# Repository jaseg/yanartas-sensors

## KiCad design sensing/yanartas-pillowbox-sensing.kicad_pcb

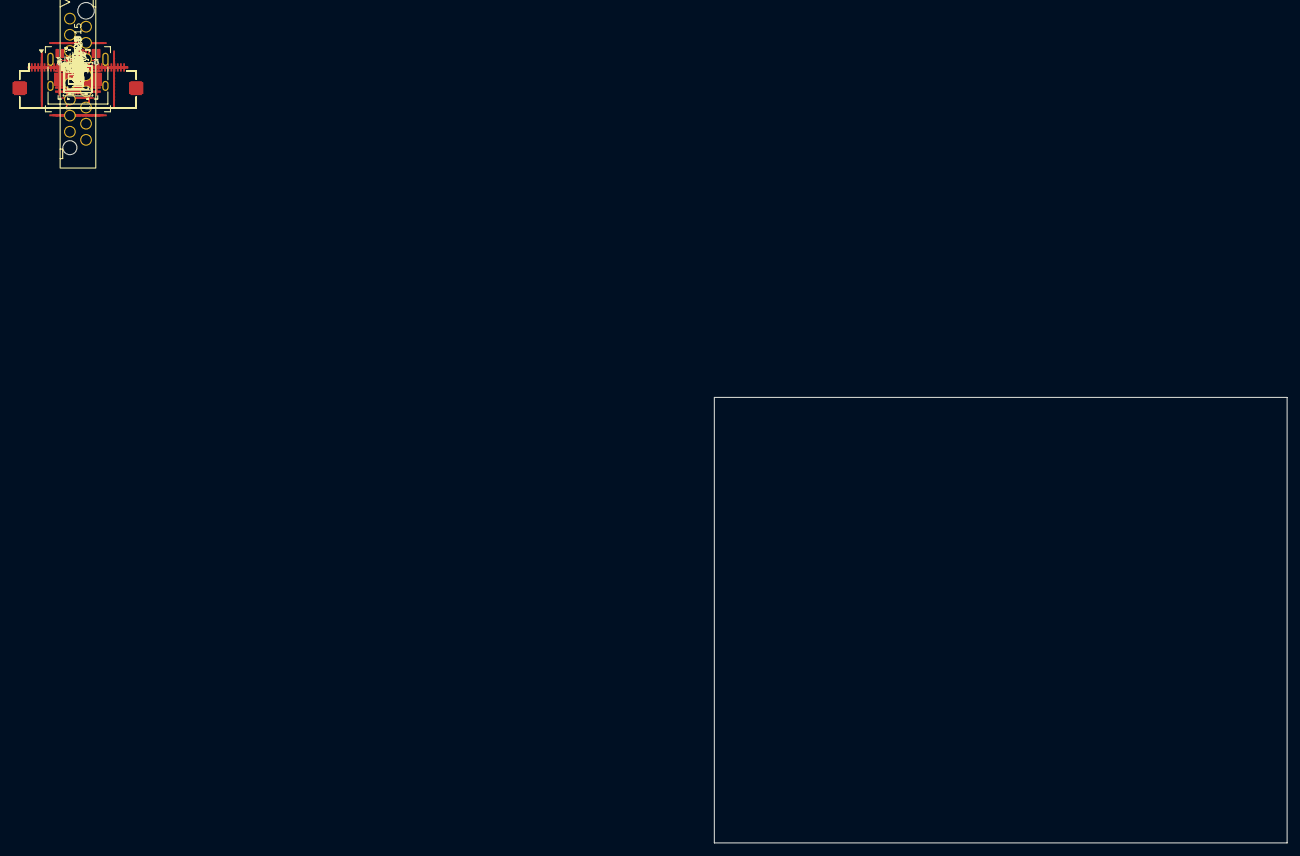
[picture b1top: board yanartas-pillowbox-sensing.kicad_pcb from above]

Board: 2 copper layers, 90.0 x 70.0 mm, 244 parts (0 on the bottom side), 263 nets, no tracks yet.

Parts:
C1, C2, C3, C4, C5, C6, C7, C8, C10, C11, C24, C42, C43, C50, C51, C52, C53, C54, C55, C56, C61, C65, C66, C67, C68, C71, C72, C73, C74, C75, C76: 220n; C_0402_1005Metric
C9, C12, C13, C14, C39, C40: 10p; C_0402_1005Metric
C15, C16, C18, C19, C20, C21, C22, C23, C25, C30, C35, C36, C37, C41, C44, C45, C46, C49, C57, C58, C59, C60, C77, C78, C79, C80, C81, C82, C83, C84, C85, C86, C87, C91, C92: 1u; C_0402_1005Metric
C17, C31, C33: 22p; C_0402_1005Metric
C26, C27: 10u/10V; C_0603_1608Metric
C28: 22u/10V; C_0805_2012Metric
C29, C32, C34, C62, C63, C64, C88: 22u/6V3; C_0805_2012Metric
C69, C70: 1n; C_0402_1005Metric
C89: 100n; C_0402_1005Metric
C90: 4u7/10V; C_0402_1005Metric
D1, D2, D3, D4, D5, D6, D7, D8: BAT15-04W; SOT-323_SC-70
D12, D13, D14: LED; LED_0603_1608Metric
J1, J2, J18: FH12S-30S-0.5SH(55); Hirose_FH12-30S-0.5SH_1x30-1MP_P0.50mm_Horizontal
J3: Wuerth WR-WST Redfit IDC; Würth_WR-WST_debug_490107671612_2x08_P2.54mm_Vertical
J5: USB_C_Receptacle_USB2.0_16P; USB_C_Receptacle_HRO_TYPE-C-31-M-12
L1, L2, L3: 2u2; CJIANG_FXL0420
R1, R2, R31, R32, R42, R43: 100; R_0402_1005Metric
R3, R4, R5, R6, R17, R18, R19, R20: 91; R_0402_1005Metric
R7, R8, R9, R10, R11, R12, R13, R14, R15, R16, R21, R22: 16; R_0402_1005Metric
R23, R25, R27, R28, R51, R99, R102, R103, R104, R124, R125: 1k; R_0402_1005Metric
R24, R26, R29, R30: 3k3; R_0402_1005Metric
R33, R35, R37, R48: 100k; R_0402_1005Metric
R34: 22k1; R_0402_1005Metric
R36: 18k2; R_0402_1005Metric
R38: 49k9; R_0402_1005Metric
R44, R45, R46, R47, R52, R53, R56, R57, R58, R59, R74, R75, R76, R77, R92, R93, R100, R101, R119, R121, R126, R127: 10k; R_0402_1005Metric
R49, R50: 5k1; R_0402_1005Metric
R54, R55: 0; R_0402_1005Metric
R60, R61, R62, R63, R64, R65, R66, R67, R68, R69, R70, R71, R72, R73, R105, R106, R109, R110, R111, R112, R113, R114, R115, R116, R117, R118: 4k7; R_0402_1005Metric
R78, R79, R80, R81, R82, R83, R84, R85: 10; R_0402_1005Metric
R94, R95, R96, R97: 47k; R_0402_1005Metric
R98, R107: 470k; R_0402_1005Metric
R122, R123: 3k9; R_0402_1005Metric
TP22: IOR7A; TestPoint_Pad_D1.0mm
TP23: IOR7B; TestPoint_Pad_D1.0mm
TP24: PA5; TestPoint_Pad_D1.0mm
TP24#2: PB6; TestPoint_Pad_D1.0mm
TP25: PB7; TestPoint_Pad_D1.0mm
U2: PI3HDX12311; Diodes_XEA32_X1-QFN-32-1EP_2.85x4.5mm_P0.4mm_EP1.75x3.4mm
U3, U9: PI3WVR41310; Diodes_ZL52_TQFN-52-1EP_3.5x9mm_P0.4mm_EP2x7.5mm
U4, U12: TMUXHS4446; Texas_WQFN-40-1EP_3x6mm_P0.4mm_EP1.7x4.5mm
U5: GW1NZ-LV1QN48C6; Gowin_QN48_QFN-48-1EP_6x6mm_P0.4mm_EP4.3x4.3mm
U6: TLV74312PDBVR; SOT-23-5
U7: TMI7003C; QFN-20-1EP_3x3mm_P0.4mm_EP1.7x1.7mm
U8: TLV74333PDBVR; SOT-23-5
U10: TMUXHS4212; Texas_RKS0020A_VQFN-20-1EP_2.5x4.5mm_P0.5mm_EP1x3mm
U13: OPA4354; TSSOP-14_4.4x5mm_P0.65mm
U15: STM32U575RGTx; LQFP-64_10x10mm_P0.5mm
U16: USBLC6-4SC6; SOT-23-6
U17: TPS51200DRC; VSON-10-1EP_3x3mm_P0.5mm_EP1.65x2.4mm
Y1: 16MHz 10p; Crystal_SMD_3225-4Pin_3.2x2.5mm

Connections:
+1V2: C15.2, C25.2, R54.1, U5.12 (VCC), U5.37 (VCC), U6.5 (OUT)
+1V8: C16.2, C34.2, L3.2, R37.1, U6.1 (IN), U6.3 (EN)
+3V3A: C30.2, C35.2, C46.2, U8.5 (OUT), U13.4 (V+), U15.13 (VDDA)
+3V3D: C19.2, C20.2, C21.2, C22.2, C23.2, C29.2, C36.2, C37.2, C41.2, C44.2, C45.2, C57.2, C59.2, C60.2, C64.2, C77.2, C78.2, C79.2, C80.2, C81.2, C82.2, C83.2, C84.2, C85.2, C86.2, C87.2, C88.2, C91.2, C92.2, L1.2, R33.1, R44.1, R46.1, R51.1, R52.1, R53.1, R55.2, R56.1, R58.1, R60.1, R62.1, R64.1, R66.1, R68.1, R70.1, R72.1, R74.1, R76.1, R98.1, R105.2, R106.2, R109.1, R111.1, R113.1, R115.1, R117.1, R122.1, R123.1, R124.1, R125.1, R126.2, U2.3 (VDD), U2.6 (VDD), U2.9 (VDD), U2.22 (VDD), U3.42 (VDD), U4.4 (VCC), U4.7 (VCC), U4.10 (VCC), U4.23 (VCC), U4.26 (VCC), U4.29 (VCC), U4.32 (VCC), U5.1 (VCCIO0), U5.36 (VCCX), U9.42 (VDD), U10.1 (RSVD1), U10.6 (VCC), U10.10 (RSVD2), U12.4 (VCC), U12.7 (VCC), U12.10 (VCC), U12.23 (VCC), U12.26 (VCC), U12.29 (VCC), U12.32 (VCC), U15.1 (VBAT), U15.19 (VDD), U15.32 (VDD), U15.48 (VDDUSB), U15.64 (VDD), U17.2 (VLDOIN), U17.7 (EN), U17.10 (VIN)
+5V: C26.2, C27.2, C28.2, J3.1, J5.A4 (VBUS), J5.A9 (VBUS), J5.B4 (VBUS), J5.B9 (VBUS), J18.3, J18.4, J18.5, J18.26, J18.27, J18.28, U7.7 (VIN2), U7.8 (EN2), U7.9 (EN1), U7.10 (VIN1), U7.18 (EN3), U7.19 (VIN3), U16.5 (VBUS)
/+3V9_INTERMEDIATE: C18.2, C32.2, L2.2, R35.1, U8.1 (IN), U8.3 (EN)
/BOOT0: R119.1, U15.60 (PH3)
/DBG1: J3.12, U15.50 (PA15)
/DBG2: J3.5, U5.6 (IOT9A/SCLK/SPMI_CLK)
/FPGA_CFG: U5.35 (IOT17B), U15.39 (PC8)
/FPGA_CLK: U5.47 (IOT10A/GCLKT_0), U15.41 (RCC_MCO)
/FPGA_DONE: R113.2, R114.1, U5.46 (IOT12A/DONE), U15.25 (PC5)
/FPGA_MODE0: R111.2, R112.1, U5.43 (IOT14A/MODE0)
/FPGA_MODE1: R109.2, R110.1, U5.42 (IOT14B/MODE1)
/FPGA_READY: R115.2, R116.1, U5.45 (IOT12B/READY)
/FPGA_RECONFIG_N: R117.2, R118.1, U5.48 (IOT9B/RECONFIG_N), U15.24 (PC4)
/FPGA_RST: U5.38 (IOT17A), U15.38 (PC7)
/FPGA_RX: U5.40 (IOT16A), U15.52 (USART3_RX)
/FPGA_SCK: U5.8 (IOT10B/GCLKC_0), U15.53 (USART3_CK)
/FPGA_TCK: J3.7, U5.3 (IOT7B/TCK/SPMI_EN/VCCEN), U15.8 (PC0)
/FPGA_TDI: J3.11, U5.5 (IOT8A/TDI/SPMI_SCLK), U15.10 (PC2)
/FPGA_TDO: J3.13, U5.7 (IOT8B/TDO), U15.11 (PC3)
/FPGA_TMS: J3.9, U5.4 (IOT7A/TMS/SPMI_SDATA), U15.9 (PC1)
/FPGA_TRIG: U5.39 (IOT16B), U15.37 (TIM3_CH1)
/FPGA_TX: U5.41 (IOT15B), U15.51 (USART3_TX)
/HOST_ALM: J18.18, U15.40 (PC9)
/HOST_ALMn: J18.17, U15.2 (PC13)
/HOST_HIPO: J18.7, U15.35 (SPI2_MISO)
/HOST_HOPI: J18.10, U15.36 (SPI2_MOSI)
/HOST_RX: J18.13, R42.2, U15.43 (USART1_RX)
/HOST_SCK: J18.8, U15.34 (SPI2_SCK)
/HOST_TX: J18.14, R43.2, U15.42 (USART1_TX)
/HOST_nCS: J18.11, U15.33 (SPI2_NSS)
/HSE_IN: C40.2, U15.5 (RCC_OSC_IN), Y1.1
/HSE_OUT: C39.2, U15.6 (RCC_OSC_OUT), Y1.3
/LED1: D12.1 (K), U15.16 (PA2)
/LED2: D13.1 (K), U15.29 (PB10)
/LED3: D14.1 (K), U15.54 (PD2)
/OUT_MUX1_OE: R44.2, R45.1, U3.5 (OE)
/OUT_MUX2_OE: R46.2, R47.1, U9.5 (OE)
/PMIC_ENABLE: J18.24, U15.58 (PB6)
/REDRV_EQHS: R68.2, R69.1, U2.13 (EQHS)
/REDRV_EQLS: R70.2, R71.1, U2.12 (EQLS)
/REDRV_FG: R66.2, R67.1, U2.28 (FG)
/REDRV_HPD: R48.2, U15.57 (PB5)
/REDRV_MODE: R72.2, R73.1, U2.16 (MODE)
/REDRV_N1SW0: R62.2, R63.1, U2.25 (N1SW0)
/REDRV_N1SW1: R60.2, R61.1, U2.29 (N1SW1)
/REDRV_SW: R64.2, R65.1, U2.15 (SW)
/RET_10N: U3.16 (D3N), U4.33 (CRX2-)
/RET_10P: U3.17 (D3P), U4.34 (CRX2+)
/RET_11N: U9.16 (D3N), U12.33 (CRX2-)
/RET_11P: U9.17 (D3P), U12.34 (CRX2+)
/RET_20N: U3.12 (D1N), U4.30 (CTX2-)
/RET_20P: U3.13 (D1P), U4.31 (CTX2+)
/RET_21N: U9.12 (D1N), U12.30 (CTX2-)
/RET_21P: U9.13 (D1P), U12.31 (CTX2+)
/RET_100N: J1.10, U3.35 (D3NA)
/RET_100P: J1.9, U3.34 (D3PA)
/RET_101N: J1.20, U3.27 (D3NB)
/RET_101P: J1.19, U3.26 (D3PB)
/RET_102N: J1.30, U3.19 (D3NC)
/RET_102P: J1.29, U3.18 (D3PC)
/RET_110N: J2.10, U9.35 (D3NA)
/RET_110P: J2.9, U9.34 (D3PA)
/RET_111N: J2.20, U9.27 (D3NB)
/RET_111P: J2.19, U9.26 (D3PB)
/RET_112N: J2.30, U9.19 (D3NC)
/RET_112P: J2.29, U9.18 (D3PC)
/RET_200N: J1.5, U3.39 (D1NA)
/RET_200P: J1.4, U3.38 (D1PA)
/RET_201N: J1.15, U3.31 (D1NB)
/RET_201P: J1.14, U3.30 (D1PB)
/RET_202N: J1.25, U3.23 (D1NC)
/RET_202P: J1.24, U3.22 (D1PC)
/RET_210N: J2.5, U9.39 (D1NA)
/RET_210P: J2.4, U9.38 (D1PA)
/RET_211N: J2.15, U9.31 (D1NB)
/RET_211P: J2.14, U9.30 (D1PB)
/RET_212N: J2.25, U9.23 (D1NC)
/RET_212P: J2.24, U9.22 (D1PC)
/SAMPLE_ADC1N: C9.2, R24.2, U13.7, U15.23 (ADC1_IN12)
/SAMPLE_ADC1P: C12.2, R26.2, U13.1, U15.22 (ADC1_IN11)
/SAMPLE_ADC2N: C13.2, R29.2, U13.14, U15.15 (ADC1_IN6)
/SAMPLE_ADC2P: C14.2, R30.2, U13.8, U15.14 (ADC1_IN5)
/SEL_L1: U10.9 (SEL), U15.28 (PB2)
/SEL_L2_0: U4.35 (CONF0), U12.35 (CONF0), U15.27 (PB1)
/SEL_L2_1: R122.2, U4.36 (CONF1), U12.36 (CONF1), U15.61 (I2C1_SCL)
/SEL_L2_2: R123.2, U4.38 (CONF2), U12.38 (CONF2), U15.62 (I2C1_SDA)
/SEL_L3_0: R126.1, U3.44 (SEL0), U9.44 (SEL0), U15.55 (PB3)
/SEL_L3_1: U3.43 (SEL1), U9.43 (SEL1), U15.56 (PB4)
/SEND_10N: U3.14 (D2N), U4.24 (CRX1-)
/SEND_10P: U3.15 (D2P), U4.25 (CRX1+)
/SEND_11N: U9.14 (D2N), U12.24 (CRX1-)
/SEND_11P: U9.15 (D2P), U12.25 (CRX1+)
/SEND_20N: U3.10 (D0N), U4.27 (CTX1-)
/SEND_20P: U3.11 (D0P), U4.28 (CTX1+)
/SEND_21N: U9.10 (D0N), U12.27 (CTX1-)
/SEND_21P: U9.11 (D0P), U12.28 (CTX1+)
/SEND_100N: J1.8, U3.37 (D2NA)
/SEND_100P: J1.7, U3.36 (D2PA)
/SEND_101N: J1.18, U3.29 (D2NB)
/SEND_101P: J1.17, U3.28 (D2PB)
/SEND_102N: J1.28, U3.21 (D2NC)
/SEND_102P: J1.27, U3.20 (D2PC)
/SEND_110N: J2.8, U9.37 (D2NA)
/SEND_110P: J2.7, U9.36 (D2PA)
/SEND_111N: J2.18, U9.29 (D2NB)
/SEND_111P: J2.17, U9.28 (D2PB)
/SEND_112N: J2.28, U9.21 (D2NC)
/SEND_112P: J2.27, U9.20 (D2PC)
/SEND_200N: J1.3, U3.41 (D0NA)
/SEND_200P: J1.2, U3.40 (D0PA)
/SEND_201N: J1.13, U3.33 (D0NB)
/SEND_201P: J1.12, U3.32 (D0PB)
/SEND_202N: J1.23, U3.25 (D0NC)
/SEND_202P: J1.22, U3.24 (D0PC)
/SEND_210N: J2.3, U9.41 (D0NA)
/SEND_210P: J2.2, U9.40 (D0PA)
/SEND_211N: J2.13, U9.33 (D0NB)
/SEND_211P: J2.12, U9.32 (D0PB)
/SEND_212N: J2.23, U9.25 (D0NC)
/SEND_212P: J2.22, U9.24 (D0PC)
/SPL_HS_1N: D3.3 (common), R10.1
/SPL_HS_1P: D2.3 (common), R9.1
/SPL_HS_2N: D7.3 (common), R22.1
/SPL_HS_2P: D6.3 (common), R21.1
/SPL_LS_1N: D4.3 (common), U13.5 (+)
/SPL_LS_1P: D1.3 (common), U13.3 (+)
/SPL_LS_2N: D8.3 (common), U13.12 (+)
/SPL_LS_2P: D5.3 (common), U13.10 (+)
/STIM_1N_A: R79.1, U5.10 (IOR2B)
/STIM_1N_B: C2.1, U2.26 (A_TXN)
/STIM_1N_C: C2.2, R11.1
/STIM_1N_R: C51.1, R79.2
/STIM_1N_RC: C51.2, U2.2 (A_RXN)
/STIM_1P_A: R78.1, U5.9 (IOR2A)
/STIM_1P_B: C1.1, U2.27 (A_TXP)
/STIM_1P_C: C1.2, R7.1
/STIM_1P_R: C24.1, R78.2
/STIM_1P_RC: C24.2, U2.1 (A_RXP)
/STIM_2N_A: R81.1, U5.34 (IOR3B)
/STIM_2N_B: C4.1, U2.23 (B_TXN)
/STIM_2N_C: C4.2, R13.1
/STIM_2N_R: C52.1, R81.2
/STIM_2N_RC: C52.2, U2.5 (B_RXN)
/STIM_2P_A: R80.1, U5.11 (IOR3A)
/STIM_2P_B: C3.1, U2.24 (B_TXP)
/STIM_2P_C: C3.2, R14.1
/STIM_2P_R: C50.1, R80.2
/STIM_2P_RC: C50.2, U2.4 (B_RXP)
/STROBE_1N_A: R85.1, U5.13 (IOR10B)
/STROBE_1N_B: C8.1, U2.17 (D_TXN)
/STROBE_1N_C: C8.2, R3.1, R5.1
/STROBE_1N_R: C56.1, R85.2
/STROBE_1N_RC: C56.2, U2.11 (D_RXN)
/STROBE_1P_A: R84.1, U5.20 (IOR10A)
/STROBE_1P_B: C7.1, U2.18 (D_TXP)
/STROBE_1P_C: C7.2, R4.2, R6.2
/STROBE_1P_R: C55.1, R84.2
/STROBE_1P_RC: C55.2, U2.10 (D_RXP)
/STROBE_2N_A: R83.1, U5.23 (IOR8B)
/STROBE_2N_B: C6.1, U2.20 (C_TXN)
/STROBE_2N_C: C6.2, C70.1, C72.1, C75.2, R17.1, R19.1, R103.1
/STROBE_2N_R: C54.1, R83.2
/STROBE_2N_RC: C54.2, U2.8 (C_RXN)
/STROBE_2P_A: R82.1, U5.24 (IOR8A)
/STROBE_2P_B: C5.1, U2.21 (C_TXP)
/STROBE_2P_C: C5.2, C70.2, C72.2, C76.2, R18.2, R20.2, R104.1
/STROBE_2P_R: C53.1, R82.2
/STROBE_2P_RC: C53.2, U2.7 (C_RXP)
/TDR_1N: C66.2, R95.1, U10.4 (A0n)
/TDR_1N_CPL: C66.1, R12.2
/TDR_1P: C61.2, R94.1, U10.3 (A0p)
/TDR_1P_CPL: C61.1, R8.2
/TDR_2N: C67.2, R97.2, U10.8 (A1n)
/TDR_2N_CPL: C67.1, R15.2
/TDR_2P: C68.2, R96.2, U10.7 (A1p)
/TDR_2P_CPL: C68.1, R16.2
/TDR_10N: U4.40 (DP0-), U10.18 (B0n)
/TDR_10P: U4.39 (DP0+), U10.19 (B0p)
/TDR_11N: U10.14 (C0n), U12.40 (DP0-)
/TDR_11P: U10.15 (C0p), U12.39 (DP0+)
/TDR_20N: U4.3 (DP1-), U10.16 (B1n)
/TDR_20P: U4.2 (DP1+), U10.17 (B1p)
/TDR_21N: U10.12 (C1n), U12.3 (DP1-)
/TDR_21P: U10.13 (C1p), U12.2 (DP1+)
/TERM_MUX1_A0: R56.2, R57.1, U4.14 (A0)
/TERM_MUX1_MODE0: R52.2, R59.1, U4.1 (MODE0)
/TERM_MUX1_MODE1: R58.2, U4.13 (MODE1)
/TERM_MUX2_A0: R74.2, R75.1, U12.14 (A0)
/TERM_MUX2_MODE0: R53.2, R77.1, U12.1 (MODE0)
/TERM_MUX2_MODE1: R76.2, U12.13 (MODE1)
/TERM_S_10N: C11.2, U4.17 (SSRX-)
/TERM_S_10P: C11.1, U4.16 (SSRX+)
/TERM_S_11N: C43.2, U12.17 (SSRX-)
/TERM_S_11P: C43.1, U12.16 (SSRX+)
/TERM_S_20N: C10.1, U4.12 (SSTX-)
/TERM_S_20P: C10.2, U4.11 (SSTX+)
/TERM_S_21N: C42.1, U12.12 (SSTX-)
/TERM_S_21P: C42.2, U12.11 (SSTX+)
/TERM_Z_10N: R2.2, U4.9 (DP3-)
/TERM_Z_10P: R2.1, U4.8 (DP3+)
/TERM_Z_11N: R32.2, U12.9 (DP3-)
/TERM_Z_11P: R32.1, U12.8 (DP3+)
/TERM_Z_20N: R1.1, U4.6 (DP2-)
/TERM_Z_20P: R1.2, U4.5 (DP2+)
/TERM_Z_21N: R31.1, U12.6 (DP2-)
/TERM_Z_21P: R31.2, U12.5 (DP2+)
/UC_NRST: C89.2, J3.14, U15.7 (NRST)
/UC_SWCLK: J3.10, U15.49 (DEBUG_JTCK-SWCLK)
/UC_SWDIO: J3.8, U15.46 (DEBUG_JTMS-SWDIO)
/USB_DM: J5.A7 (D-), J5.B7 (D-), U15.44 (USB_OTG_FS_DM), U16.1 (I/O1), U16.6 (I/O4)
/USB_DP: J5.A6 (D+), J5.B6 (D+), U15.45 (USB_OTG_FS_DP), U16.3 (I/O2), U16.4 (I/O3)
/VBIAS_A: R102.2, R103.2, R127.1, U15.17 (OPAMP1_VOUT)
/VBIAS_K: R99.2, R104.2, R121.1, U15.26 (OPAMP2_VOUT)
/VBIAS_REF: R98.2, R107.1, R121.2, R127.2, U17.1 (REFIN)
/~OUT_ACT: J18.20, U15.3 (PC14)
/~OUT_ALARM: J18.21, U15.20 (PA4)
/~OUT_SECURE: J18.23, U15.4 (PC15)
GND: C15.1, C16.1, C17.2, C18.1, C19.1, C20.1, C21.1, C22.1, C23.1, C25.1, C26.1, C27.1, C28.1, C29.1, C30.1, C31.2, C32.1, C33.2, C34.1, C35.1, C36.1, C37.1, C39.1, C40.1, C41.1, C44.1, C45.1, C46.1, C49.1, C57.1, C58.1, C59.1, C60.1, C62.1, C63.1, C64.1, C65.1, C73.1, C74.1, C75.1, C76.1, C77.1, C78.1, C79.1, C80.1, C81.1, C82.1, C83.1, C84.1, C85.1, C86.1, C87.1, C88.1, C89.1, C90.2, C91.1, C92.1, J1.1, J1.6, J1.11, J1.16, J1.21, J1.26, J1.MP (MountPin), J2.1, J2.6, J2.11, J2.16, J2.21, J2.26, J2.MP (MountPin), J3.3, J3.6, J3.15, J3.16, J5.A1 (GND), J5.A12 (GND), J5.B1 (GND), J5.B12 (GND), J5.SH (SHIELD), J18.1, J18.2, J18.6, J18.9, J18.12, J18.15, J18.16, J18.19, J18.22, J18.25, J18.29, J18.30, J18.MP (MountPin), R34.2, R36.2, R38.2, R45.2, R47.2, R49.2, R50.2, R57.2, R59.2, R61.2, R63.2, R65.2, R67.2, R69.2, R71.2, R73.2, R75.2, R77.2, R107.2, R110.2, R112.2, R114.2, R116.2, R118.2, R119.2, U2.14 (GND), U2.30 (GND), U2.33 (GND), U3.53 (GND), U4.15 (GND), U4.18 (GND), U4.37 (GND), U4.41 (GND), U5.2 (VSS), U5.26 (VSS), U5.44 (IOT13A/JTAGSEL_N), U5.49 (VSS), U6.2 (GND), U7.21 (GND), U8.2 (GND), U9.53 (GND), U10.2 (OEn), U10.5 (GND), U10.11 (GND), U10.20 (GND), U10.21 (GND), U12.15 (GND), U12.18 (GND), U12.37 (GND), U12.41 (GND), U13.11 (V-), U15.12 (VSSA), U15.18 (VSS), U15.31 (VSS), U15.47 (VSS), U15.63 (VSS), U16.2 (GND), U17.4 (GND), U17.8 (GND), U17.11 (GND), Y1.2 (G), Y1.4 (G)
GNDS: C58.2, C62.2, C63.2, R23.2, R25.2, R27.2, R28.2, R92.2, R93.2, R94.2, R95.2, R96.1, R97.1, R100.2, R101.2, U17.3 (VO), U17.5 (VOSNS)
unnamed: C69.1, C71.1, C74.2, R102.1
unnamed: C69.2, C71.2, C73.2, R99.1
unnamed: D1.1 (A), D2.1 (A), R5.2
unnamed: D1.2 (K), D2.2 (K), R4.1
unnamed: D3.1 (A), D4.1 (A), R3.2
unnamed: D3.2 (K), D4.2 (K), R6.1
unnamed: D5.1 (A), D6.1 (A), R17.2
unnamed: D5.2 (K), D6.2 (K), R18.1
unnamed: D7.1 (A), D8.1 (A), R19.2
unnamed: D7.2 (K), D8.2 (K), R20.1
unnamed: D12.2 (A), R51.2
unnamed: D13.2 (A), R124.2
unnamed: D14.2 (A), R125.2
unnamed: J3.2, R43.1
unnamed: J3.4, R42.1
unnamed: J5.A5 (CC1), R49.1
unnamed: J5.B5 (CC2), R50.1
unnamed: R7.2, R8.1, R9.2, R92.1
unnamed: R10.2, R11.2, R12.1, R93.1
unnamed: R14.2, R16.1, R21.2, R100.1
unnamed: R13.2, R15.1, R22.2, R101.1
unnamed: R106.1, U2.32 (DDC_SCL)
unnamed: R105.1, U2.31 (DDC_SDA)
unnamed: R48.1, U2.19 (HPD)
unnamed: TP22.1 (1_1), U5.27 (IOR7A)
unnamed: TP23.1 (1_1), U5.21 (IOR7B)
unnamed: C49.2, R54.2, R55.1, U5.25 (VCCIO1)
unnamed: C17.1, R33.2, R34.1, U7.14 (FB1)
unnamed: C31.1, R35.2, R36.1, U7.3 (FB2)
unnamed: C33.1, R37.2, R38.1, U7.2 (FB3)
unnamed: L1.1, U7.11 (LX1)
unnamed: L2.1, U7.6 (LX2)
unnamed: L3.1, U7.20 (LX3)
unnamed: C12.1, R25.1, R26.1, U13.2 (-)
unnamed: C9.1, R23.1, R24.1, U13.6 (-)
unnamed: C14.1, R28.1, R30.1, U13.9 (-)
unnamed: C13.1, R27.1, R29.1, U13.13 (-)
unnamed: TP24.1 (1_1), U15.21 (PA5)
unnamed: TP25.1 (1_1), U15.59 (PB7)
unnamed: C90.1, U15.30 (VCAP)
unnamed: C65.2, U17.6 (REFOUT)
